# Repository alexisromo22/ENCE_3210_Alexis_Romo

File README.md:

# ENCE_3210_Alexis_Romo

Hello World

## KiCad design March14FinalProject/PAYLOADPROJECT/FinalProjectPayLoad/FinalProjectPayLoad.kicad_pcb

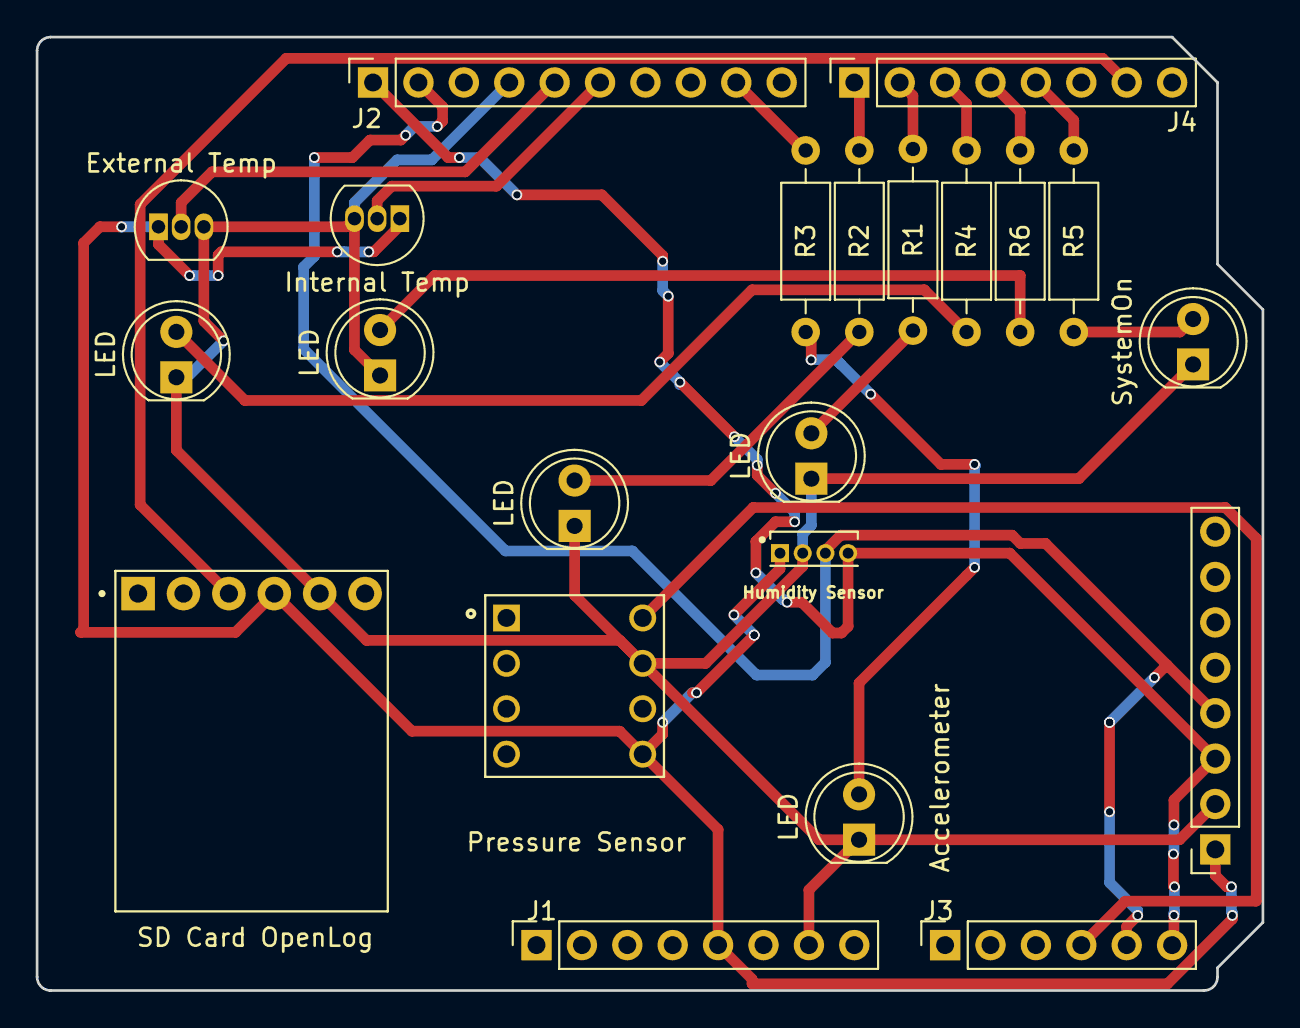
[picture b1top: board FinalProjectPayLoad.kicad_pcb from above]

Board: 2 copper layers, 68.6 x 53.3 mm, 22 parts (0 on the bottom side), 20 nets.

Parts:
Accelerometer: Conn_01x08; PinSocket_1x08_P2.54mm_Vertical
External Temp: TSIC306-TO92; TO-92_Inline
Humidity Sensor: Conn_01x04; SIP191W41P127L490H390Q4
Internal Temp: TSIC306-TO92; TO-92_Inline
J1: Power; PinSocket_1x08_P2.54mm_Vertical
J2: Digital/PWM; PinSocket_1x10_P2.54mm_Vertical
J3: Analog; PinSocket_1x06_P2.54mm_Vertical
J4: Digital/PWM; PinSocket_1x08_P2.54mm_Vertical
LED: LD271; LED_D5.0mm
LED#2, LED#3, LED#4, LED#5: LD271; LED_D5.0mm
Pressure Sensor: 1-2199298-2; TE_1-2199298-2
R1, R2, R3, R4, R5, R6: 330; R_Axial_DIN0207_L6.3mm_D2.5mm_P10.16mm_Horizontal
SD Card OpenLog: Conn_01x06; MODULE_DEV-13712
SystemOn: LD271; LED_D5.0mm

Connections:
+5V: Accelerometer.1, External Temp.1 (V+), Humidity Sensor.1, Internal Temp.1 (V+), J1.5, Pressure Sensor.5, SD Card OpenLog.4
/4: J4.4, R6.2
/7: J4.1, R2.2
/12: Internal Temp.2 (Signal), J2.6
/12C_SCL: Accelerometer.3, Humidity Sensor.4, J2.1, J3.6
/12C_SDA: Accelerometer.4, Humidity Sensor.3, J2.2, J3.5
/13: External Temp.2 (Signal), J2.5
/*3: J4.5, R5.2
/*5: J4.3, R4.2
/*6: J4.2, R1.2
/*9: J2.9, R3.2
/A3: J3.4, Pressure Sensor.8
/TX: J4.7, SD Card OpenLog.3
GND: Accelerometer.2, External Temp.3 (GND), Humidity Sensor.2, Internal Temp.3 (GND), J1.6, J1.7, J2.4, LED.1 (K), LED#2.1 (K), LED#3.1 (K), LED#4.1 (K), LED#5.1 (K), Pressure Sensor.7, SD Card OpenLog.5, SystemOn.1 (K)
unnamed: LED#4.2 (A), R1.1
unnamed: LED#5.2 (A), R2.1
unnamed: LED#2.2 (A), R3.1
unnamed: LED.2 (A), R4.1
unnamed: R5.1, SystemOn.2 (A)
unnamed: LED#3.2 (A), R6.1

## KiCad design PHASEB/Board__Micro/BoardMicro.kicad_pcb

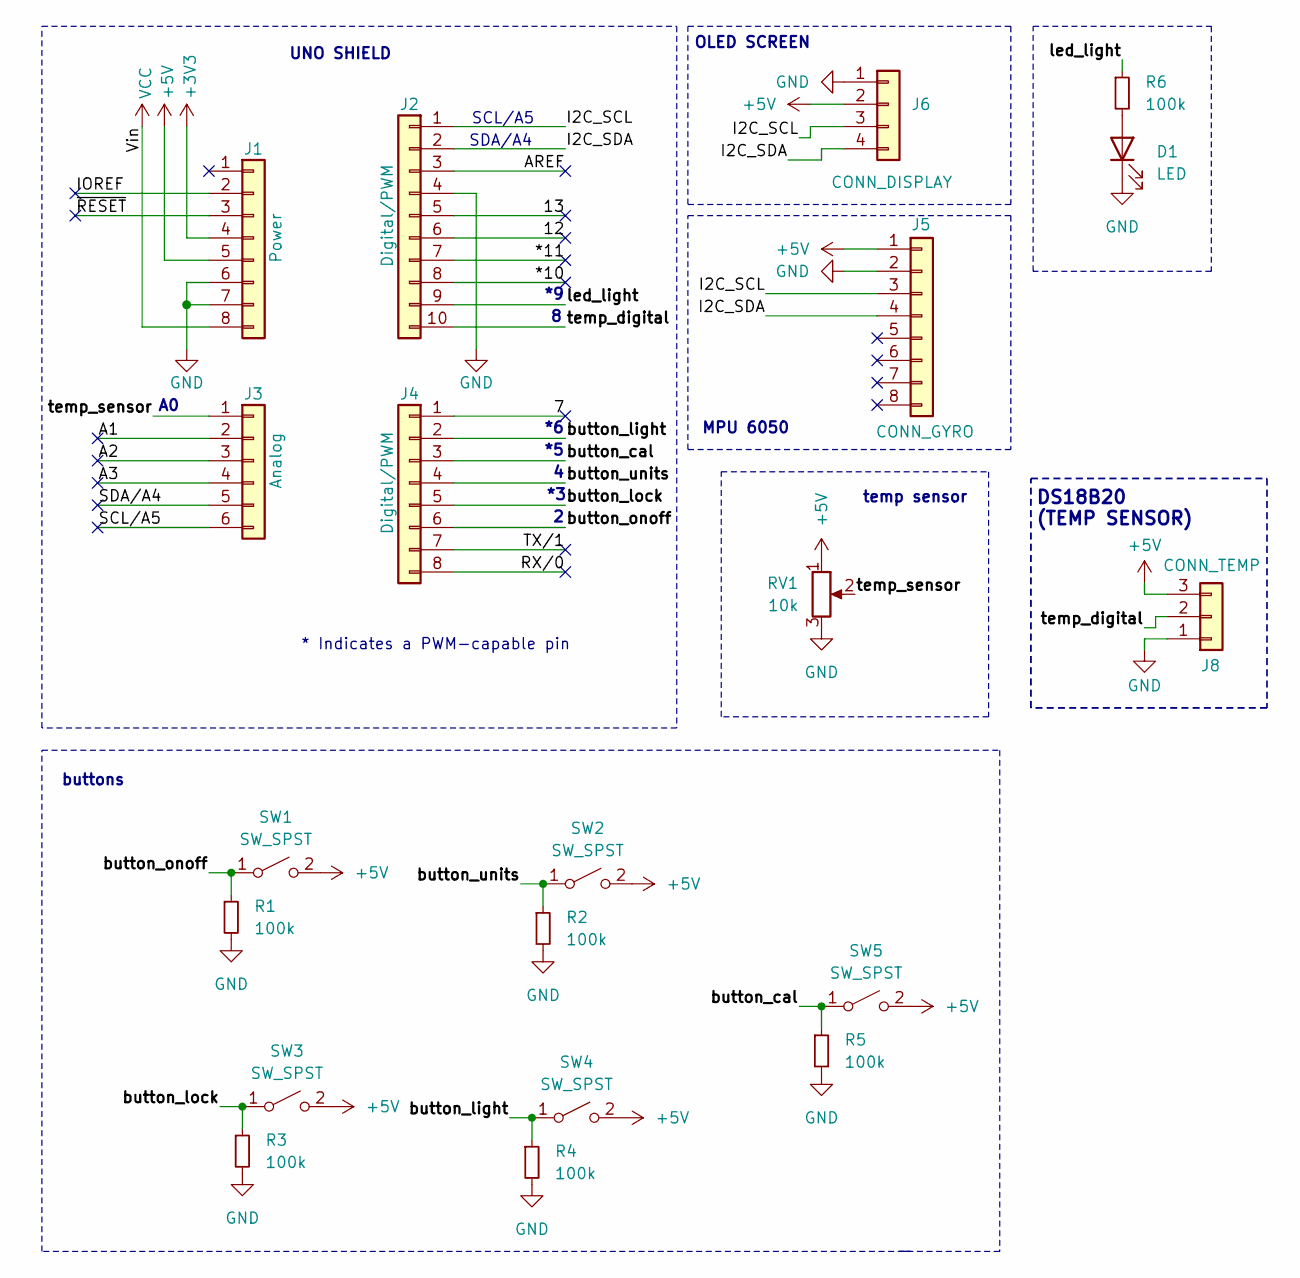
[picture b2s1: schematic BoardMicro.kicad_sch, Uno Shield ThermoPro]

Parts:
D1: LED; LED_D5.0mm
J1: Power; PinSocket_1x08_P2.54mm_Vertical
J2: Digital/PWM; PinSocket_1x10_P2.54mm_Vertical
J3: Analog; PinSocket_1x06_P2.54mm_Vertical
J4: Digital/PWM; PinSocket_1x08_P2.54mm_Vertical
J5: CONN_GYRO; PinSocket_1x08_P2.54mm_Vertical
J6: CONN_DISPLAY; PinSocket_1x04_P2.54mm_Vertical
J8: CONN_TEMP; JST_XH_B3B-XH-A_1x03_P2.50mm_Vertical
R1, R2, R3, R4, R5, R6: 100k; R_Axial_DIN0207_L6.3mm_D2.5mm_P10.16mm_Horizontal
RV1: 10k; Potentiometer_Bourns_3386P_Vertical
SW1, SW2, SW3, SW4, SW5: SW_SPST; SW_PUSH_6mm

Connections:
+3V3: J1.4
+5V: J1.5, J5.1, J6.2, J8.3, RV1.1, SW1.2 (B), SW2.2 (B), SW3.2 (B), SW4.2 (B), SW5.2 (B); also elsewhere on the board
/7: J4.1
/12: J2.6
/13: J2.5
/*10: J2.8
/*11: J2.7
/A1: J3.2
/A2: J3.3
/A3: J3.4
/AREF: J2.3
/I2C_SCL: J2.1, J5.3, J6.3
/I2C_SDA: J2.2, J5.4, J6.4
/IOREF: J1.2
/RX/0: J4.8
/SCL/A5: J3.6
/SDA/A4: J3.5
/TX/1: J4.7
/button_cal: J4.3, R5.1, SW5.1 (A)
/button_light: J4.2, R4.1, SW4.1 (A)
/button_lock: J4.5, R3.1, SW3.1 (A)
/button_onoff: J4.6, R1.1, SW1.1 (A)
/button_units: J4.4, R2.1, SW2.1 (A)
/led_light: J2.9, R6.1
/temp_digital: J2.10, J8.2; also elsewhere on the board
/temp_sensor: J3.1, RV1.2
/~RESET: J1.3
GND: D1.1 (K), J1.6, J1.7, J2.4, J5.2, J6.1, J8.1, R1.2, R2.2, R3.2, R4.2, R5.2, RV1.3; also elsewhere on the board
unnamed: D1.2 (A), R6.2
VCC: J1.8

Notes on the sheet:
buttons
DS18B20 (TEMP SENSOR)
OLED SCREEN
SDA/A4
UNO SHIELD
SCL/A5
MPU 6050
* Indicates a PWM-capable pin
temp sensor

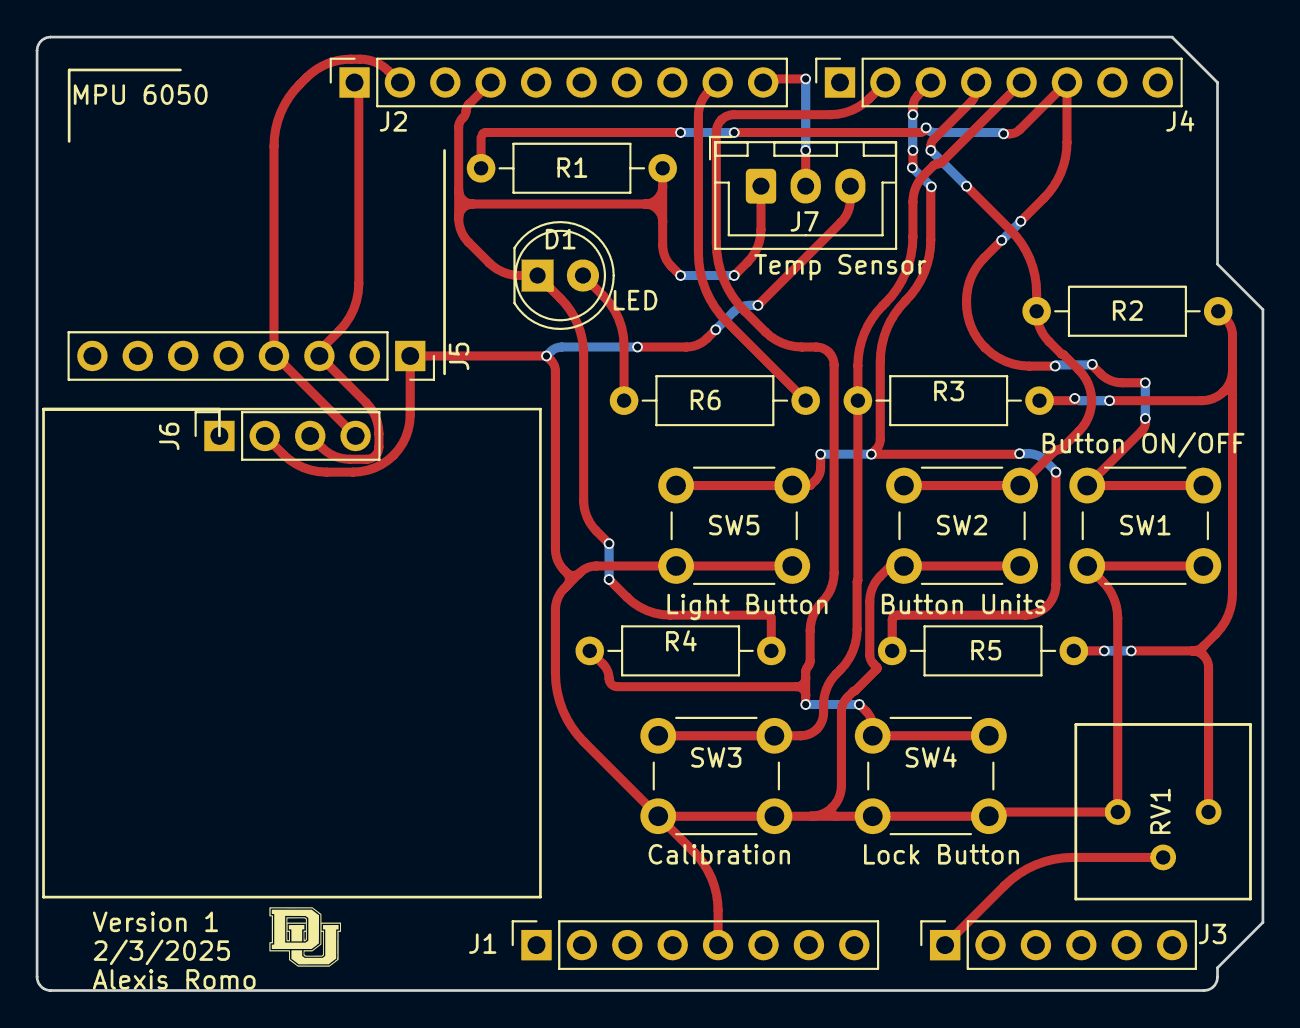
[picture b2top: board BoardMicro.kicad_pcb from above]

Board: 2 copper layers, 68.6 x 53.3 mm, 20 parts (0 on the bottom side), 13 nets.

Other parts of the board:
J7: CONN_TEMP; JST_XH_B3B-XH-A_1x03_P2.50mm_Vertical

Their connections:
+5V: J7.3; also elsewhere on the board
/temp_digital: J7.2; also elsewhere on the board
GND: J7.1; also elsewhere on the board
